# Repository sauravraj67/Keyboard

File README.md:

# Keyboard

I am making a custom keyboard for myself , it is based on 60% keyboard layout . I will also have nobs for volume and brightness control. PCB is designed in kicad and 3D covers are made in fusion.
## Features

- Base on Raspberry pico W
- Has 60% Keyboard Matrix
- Has 2 Rotor Encoder For voulem and brigtness controll 
  ### Schematic
   HOURS Worked :- 5.2 hours  <br>
So i firstly thought what would be the features of my keyboard . It is a simple mechanical keyboard in 60% layout that uses keyboard matrix so that it uses less gpio pins and diodes are used to preventing ghosting. and i will also use hot-swap so that if i want i can change the keys without soldering or de soldering. Prior to that it will has 2 rotor encoders to control the volume and brightness.

So firstly i imported all the footprints and layout of components which would be used.

Then i started with making the keyboard matrix . I used references from the web for the layout of the switches also i assigned the key sizes accordingly . I also added stabilizers for keys whose width was over 1.75 U. then i made the connection of rows and columns of the matrix .
After it i added the 2 rotor encoder ,stabilizers with required size and raspberry pi pico and made the connections of the rotor encoders to the analog pins anf colums and rows to the gpio pins.

The most time consuming part was to make the matrix because firstly you have to decide which key would be assigned to which column because after column one there are more columns then the switches over to that the sizes of each switches aren't same so i have to take a proper look on that as well . Final Look 

  ###  PCB Design  
  
   ## PCB Layout   
     HOURS Worked :- 3.5 Hours  <br>
   So i loaded the pcb with all the components again the hardest and most time consuming part was re arranging the keyboard matrix. First i added the satirizers to there responded key size , then i started arranging all the keys as per my layout at 19.05 mm and 0.7937mm grid so that the keys could easy snap with each other but many a times i had difficulties doing so , then i used different sized grides for that after i arranged all the keys then i started with arrangement of the resistors as per there connected switches in such a way that it would turn out to be a ease to me while i rout. Final look

 ## Routing    
 Hours Worked :- 3.1 <br>

I started with routing the Diodes to the swich first then after that I routed the Rows and columns and then connected it to the MCU after which I made the connections for the Rotor encoders as well . I tried to make as clean routs as possible and used both side of the PCB to rout. Somethimes there wasn;t a way to rout so I had to make some changes onto the previous rout and this ishow the final PCB looks 

<br>

### Made the case 

Hours worked :-  4.25 Hours  

So I Firstly took the dimensions of the PCB and moved to fusion for the case design firstly i started with designing the Base for that I created sketch for the base added a base height of 3mm and then moved to calculate the PCB height which will be 4.6mm (3mm for hot swap and 1.6 mm for PCB) and i added .4 mm of free space and modeled the base. Base width was 10mm less by each side in inner meserement so that the PCB can fix into in. Sketch 

BASE 

Then I updated the schematics with exact PCB dimensions so that PCB alight perfectly with the base and added holes for the screws onto it. Prior to that i extrude the base so that to fix the above components of the pcb in the base (distance from top of PCB to mid of key switch is 5mm) Top layer would be 1.1mm so i extruded 3.9mm because few components were not fitting in the Base such as the USB-B type

Then I added a hole for the USB type connection and polished the Base By curing it's side

After that i stated with making the Top layer i added the keyboard layout sketches and aligned it perfectly to the keys and made the top layer by adding them and added holes for the rotor encoder .First i thought just to add a small circular hole for the top but later i found that it would not fix well as come part of rotor encoder base was colliding with the top so i made square holes for it  . Final Look 

<br>

# Bill of Materials (BOM)

| Index | Component | Qty | Cost (USD) | Link |
|---|---|---|---|---|
| 1 | Mechanical Keyboard Switches | 2 packs | $10.62 | https://www.amazon.in/gp/product/B0G39H2G4H |
| 2 | Meckeys Shipping | 1 | $1.07 | https://meckeys.com |
| 3 | Raspberry Pi Pico SC0917 | 1 | $5.79 | https://www.amazon.in/gp/product/B0B69KZBD8 |
| 4 | Keycap Set | 1 | $10.73 | https://www.amazon.in/gp/product/B0GFNPXVJL |
| 5 | Stabilizers | 1 | $10.74 | https://meckeys.com/shop/accessories/keyboard-accessories/more/glorious-goat-stabilizers/ |
| 6 | Kailh Hot Swap Sockets | 7 packs | $5.41 | https://meckeys.com/shop/accessories/keyboard-accessories/key-switches/kailh-hot-swap-socket/ |
| 7 | PCB + Shipping (JLCPCB) | 1 | $35.98 | https://jlcpcb.com |
| 8 | Rotary Encoder | 1 pack | $1.84 | https://www.amazon.in/gp/product/B0888RWNM1 |
| 9 | Headset / Connector | 1 | $0.79 | https://www.amazon.in/gp/product/B0BB86CQSJ |
| 10 | M3 Screws | 1 | $2.20 | https://www.amazon.in/dp/B07XFP714Z |
| 11 | 3D Printed Case | 1 | 0 | Made by Cookie With Coffee from #printing-legion |

---

## Total Estimated Cost

# ~$84.17 USD

## Hardware
- Raspberry Pico 
- Cherry MX compatible Switches
- Diode
- 2 layer PCB + 3D Case
- 2 Rotor Encoder
- Hot Swap
- Key Caps

## Firmware
- It is Based on KMK and Circuit Python

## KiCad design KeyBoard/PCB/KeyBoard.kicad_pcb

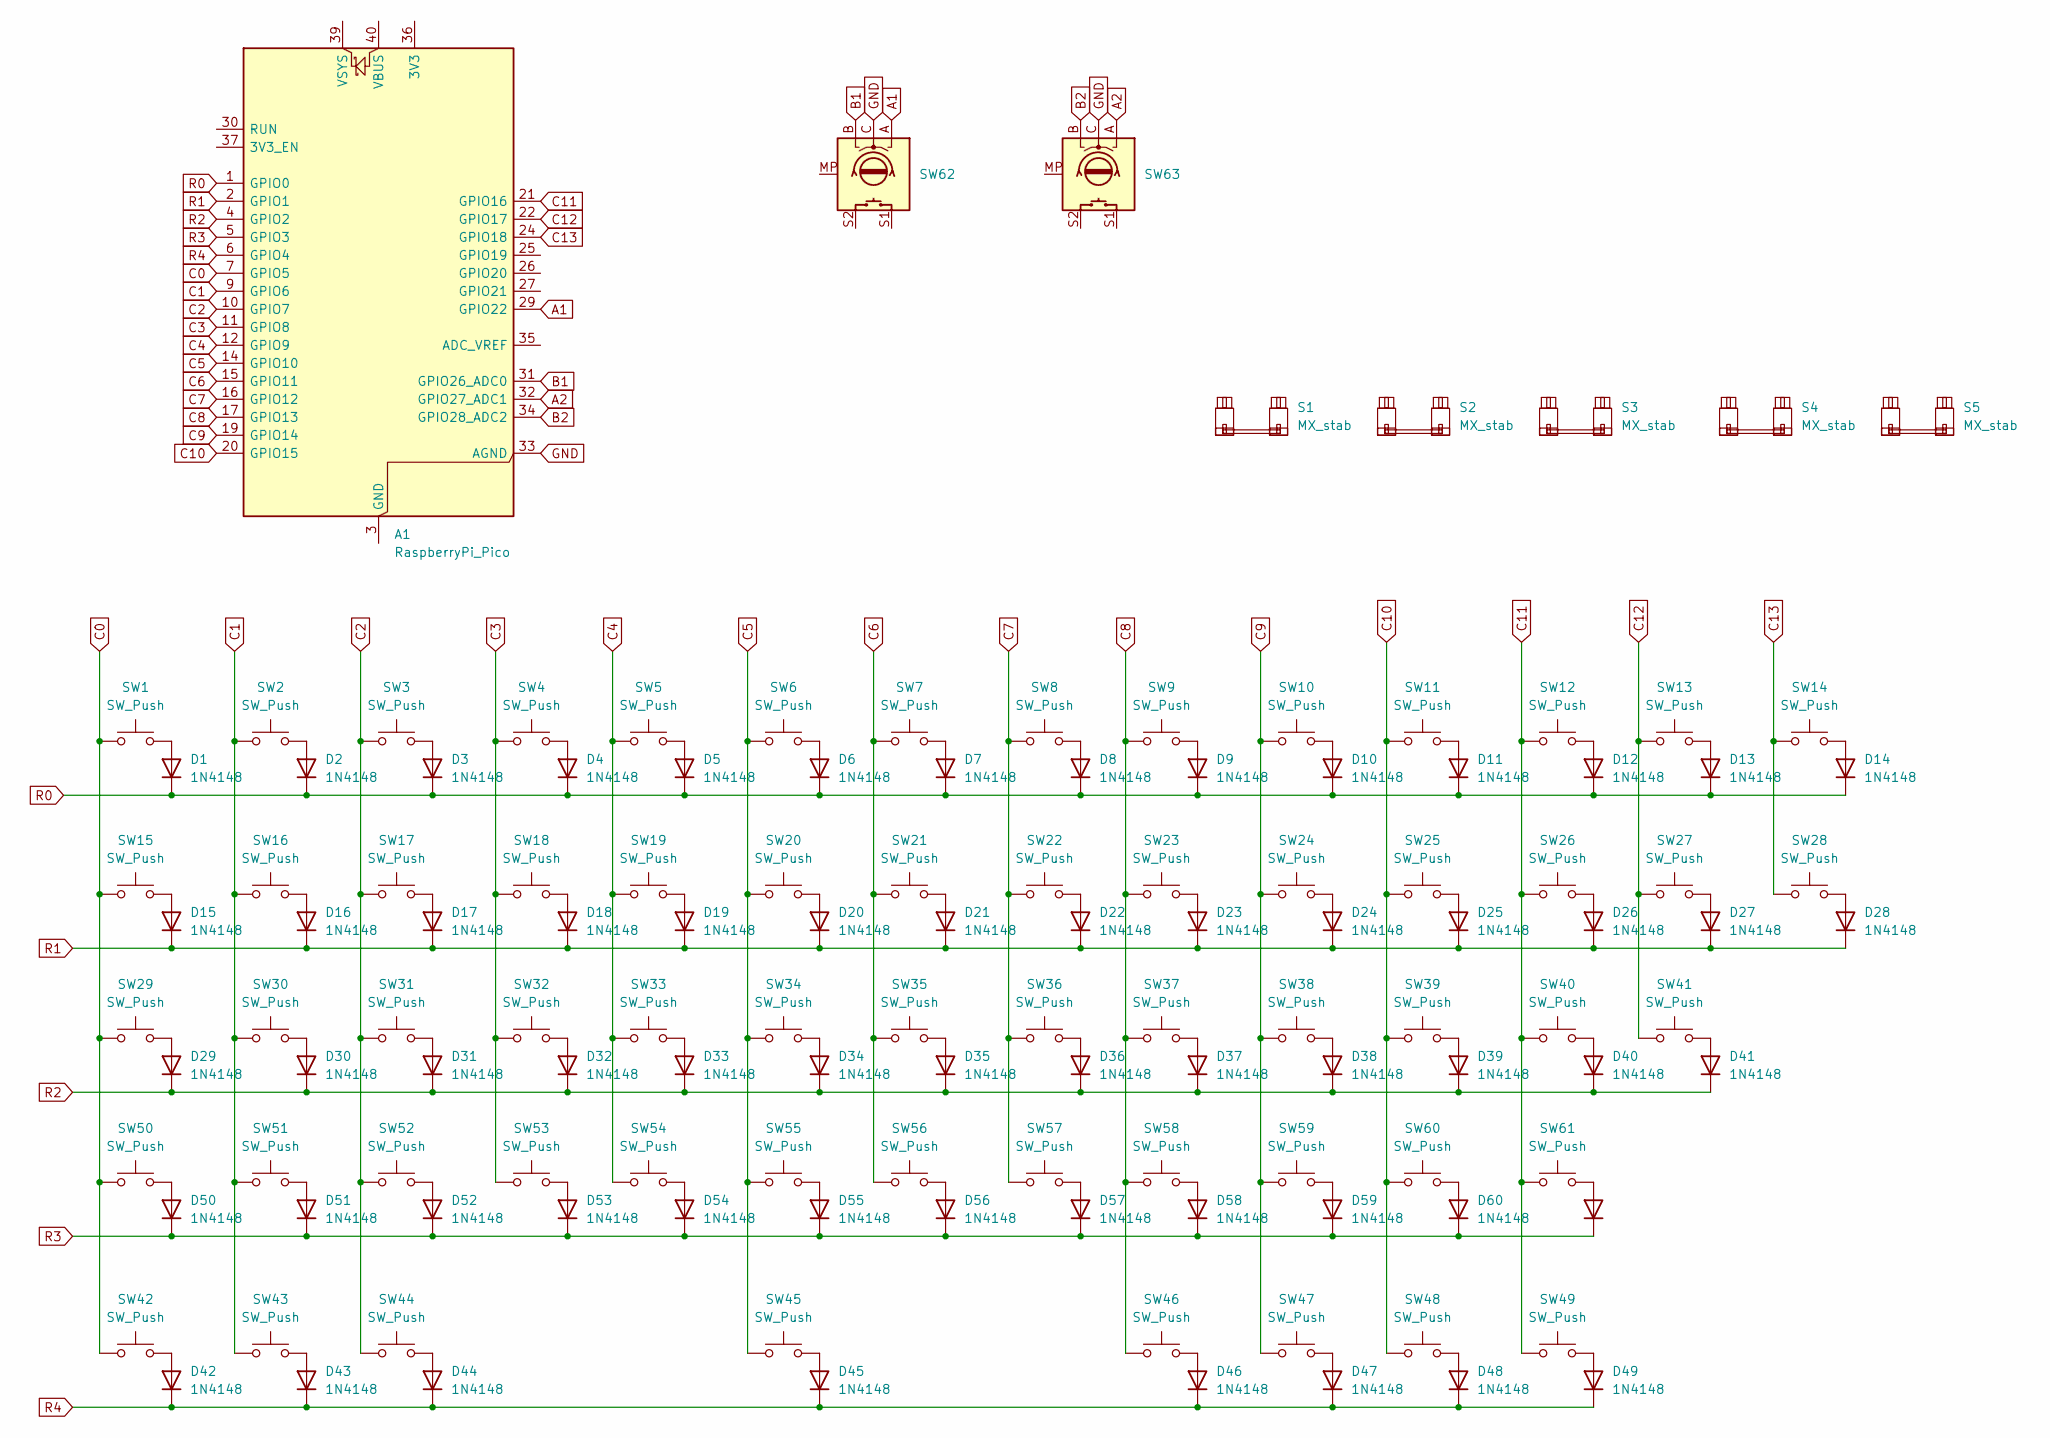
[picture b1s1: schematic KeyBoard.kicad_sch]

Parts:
A1: RaspberryPi_Pico; RaspberryPi_Pico_Common_Unspecified
D1, D2, D3, D4, D5, D6, D7, D8, D9, D10, D11, D12, D13, D14, D15, D16, D17, D18, D19, D20, D21, D22, D23, D24, D25, D26, D27, D28, D29, D30, D31, D32, D33, D34, D35, D36, D37, D38, D39, D40, D41, D42, D43, D44, D45, D46, D47, D48, D49, D50, D51, D52, D53, D54, D55, D56, D57, D58, D59, D60, D61: 1N4148; D_DO-35_SOD27_P7.62mm_Horizontal
S1: MX_stab; STAB_MX_2u
S2, S3: MX_stab; STAB_MX_2.25u
S4: MX_stab; STAB_MX_2.75u
S5: MX_stab; STAB_MX_6.25u
SW1, SW2, SW3, SW4, SW5, SW6, SW7, SW8, SW9, SW10, SW11, SW12, SW13, SW16, SW17, SW18, SW19, SW20, SW21, SW22, SW23, SW24, SW25, SW26, SW27, SW30, SW31, SW32, SW33, SW34, SW35, SW36, SW37, SW38, SW39, SW40, SW51, SW52, SW53, SW54, SW55, SW56, SW57, SW58, SW59, SW60: SW_Push; MX100H
SW14: SW_Push; MX200H
SW15, SW28: SW_Push; MX150H
SW29: SW_Push; MX175H
SW41, SW50: SW_Push; MX225HR
SW42, SW43, SW44, SW46, SW47, SW48, SW49: SW_Push; MX125H
SW45: SW_Push; MX625H
SW61: SW_Push; MX275H
SW62, SW63: RotaryEncoder_Switch_MP; RotaryEncoder_Alps_EC11E-Switch_Vertical_H20mm

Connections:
A1: A1.29 (GPIO22), SW62.A
A2: A1.32 (GPIO27_ADC1), SW63.A
B1: A1.31 (GPIO26_ADC0), SW62.B
B2: A1.34 (GPIO28_ADC2), SW63.B
C0: A1.7 (GPIO5), SW1.1, SW15.1, SW29.1, SW42.1, SW50.1
C1: A1.9 (GPIO6), SW2.1, SW16.1, SW30.1, SW43.1, SW51.1
C2: A1.10 (GPIO7), SW3.1, SW17.1, SW31.1, SW44.1, SW52.1
C3: A1.11 (GPIO8), SW4.1, SW18.1, SW32.1, SW53.1
C4: A1.12 (GPIO9), SW5.1, SW19.1, SW33.1, SW54.1
C5: A1.14 (GPIO10), SW6.1, SW20.1, SW34.1, SW45.1, SW55.1
C6: A1.15 (GPIO11), SW7.1, SW21.1, SW35.1, SW56.1
C7: A1.16 (GPIO12), SW8.1, SW22.1, SW36.1, SW57.1
C8: A1.17 (GPIO13), SW9.1, SW23.1, SW37.1, SW46.1, SW58.1
C9: A1.19 (GPIO14), SW10.1, SW24.1, SW38.1, SW47.1, SW59.1
C10: A1.20 (GPIO15), SW11.1, SW25.1, SW39.1, SW48.1, SW60.1
C11: A1.21 (GPIO16), SW12.1, SW26.1, SW40.1, SW49.1, SW61.1
C12: A1.22 (GPIO17), SW13.1, SW27.1, SW41.1
C13: A1.24 (GPIO18), SW14.1, SW28.1
GND: A1.33 (AGND), SW62.C, SW63.C
unnamed: A1.3 (GND), A1.8 (GND), A1.13 (GND), A1.18 (GND), A1.23 (GND), A1.28 (GND), A1.38 (GND)
unnamed: D1.2 (A), SW1.2
unnamed: D2.2 (A), SW2.2
unnamed: D3.2 (A), SW3.2
unnamed: D4.2 (A), SW4.2
unnamed: D5.2 (A), SW5.2
unnamed: D6.2 (A), SW6.2
unnamed: D7.2 (A), SW7.2
unnamed: D8.2 (A), SW8.2
unnamed: D9.2 (A), SW9.2
unnamed: D10.2 (A), SW10.2
unnamed: D11.2 (A), SW11.2
unnamed: D12.2 (A), SW12.2
unnamed: D13.2 (A), SW13.2
unnamed: D14.2 (A), SW14.2
unnamed: D15.2 (A), SW15.2
unnamed: D16.2 (A), SW16.2
unnamed: D17.2 (A), SW17.2
unnamed: D18.2 (A), SW18.2
unnamed: D19.2 (A), SW19.2
unnamed: D20.2 (A), SW20.2
unnamed: D21.2 (A), SW21.2
unnamed: D22.2 (A), SW22.2
unnamed: D23.2 (A), SW23.2
unnamed: D24.2 (A), SW24.2
unnamed: D25.2 (A), SW25.2
unnamed: D26.2 (A), SW26.2
unnamed: D27.2 (A), SW27.2
unnamed: D28.2 (A), SW28.2
unnamed: D29.2 (A), SW29.2
unnamed: D30.2 (A), SW30.2
unnamed: D31.2 (A), SW31.2
unnamed: D32.2 (A), SW32.2
unnamed: D33.2 (A), SW33.2
unnamed: D34.2 (A), SW34.2
unnamed: D35.2 (A), SW35.2
unnamed: D36.2 (A), SW36.2
unnamed: D37.2 (A), SW37.2
unnamed: D38.2 (A), SW38.2
unnamed: D39.2 (A), SW39.2
unnamed: D40.2 (A), SW40.2
unnamed: D41.2 (A), SW41.2
unnamed: D42.2 (A), SW42.2
unnamed: D43.2 (A), SW43.2
unnamed: D44.2 (A), SW44.2
unnamed: D45.2 (A), SW45.2
unnamed: D46.2 (A), SW46.2
unnamed: D47.2 (A), SW47.2
unnamed: D48.2 (A), SW48.2
unnamed: D49.2 (A), SW49.2
unnamed: D50.2 (A), SW50.2
unnamed: D51.2 (A), SW51.2
unnamed: D52.2 (A), SW52.2
unnamed: D53.2 (A), SW53.2
unnamed: D54.2 (A), SW54.2
unnamed: D55.2 (A), SW55.2
unnamed: D56.2 (A), SW56.2
unnamed: D57.2 (A), SW57.2
unnamed: D58.2 (A), SW58.2
unnamed: D59.2 (A), SW59.2
unnamed: D60.2 (A), SW60.2
unnamed: D61.2 (A), SW61.2
R0: A1.1 (GPIO0), D1.1 (K), D2.1 (K), D3.1 (K), D4.1 (K), D5.1 (K), D6.1 (K), D7.1 (K), D8.1 (K), D9.1 (K), D10.1 (K), D11.1 (K), D12.1 (K), D13.1 (K), D14.1 (K)
R1: A1.2 (GPIO1), D15.1 (K), D16.1 (K), D17.1 (K), D18.1 (K), D19.1 (K), D20.1 (K), D21.1 (K), D22.1 (K), D23.1 (K), D24.1 (K), D25.1 (K), D26.1 (K), D27.1 (K), D28.1 (K)
R2: A1.4 (GPIO2), D29.1 (K), D30.1 (K), D31.1 (K), D32.1 (K), D33.1 (K), D34.1 (K), D35.1 (K), D36.1 (K), D37.1 (K), D38.1 (K), D39.1 (K), D40.1 (K), D41.1 (K)
R3: A1.5 (GPIO3), D50.1 (K), D51.1 (K), D52.1 (K), D53.1 (K), D54.1 (K), D55.1 (K), D56.1 (K), D57.1 (K), D58.1 (K), D59.1 (K), D60.1 (K), D61.1 (K)
R4: A1.6 (GPIO4), D42.1 (K), D43.1 (K), D44.1 (K), D45.1 (K), D46.1 (K), D47.1 (K), D48.1 (K), D49.1 (K)

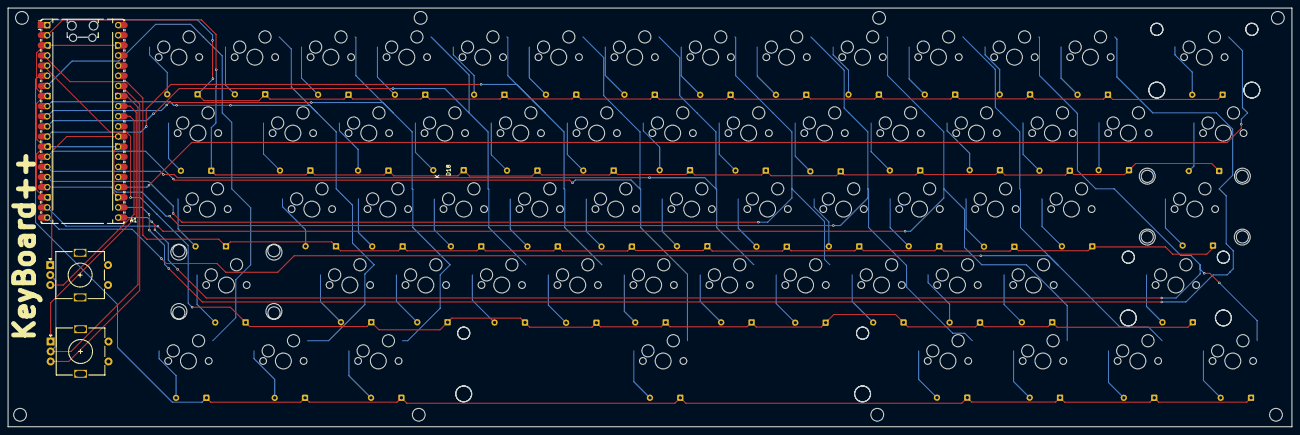
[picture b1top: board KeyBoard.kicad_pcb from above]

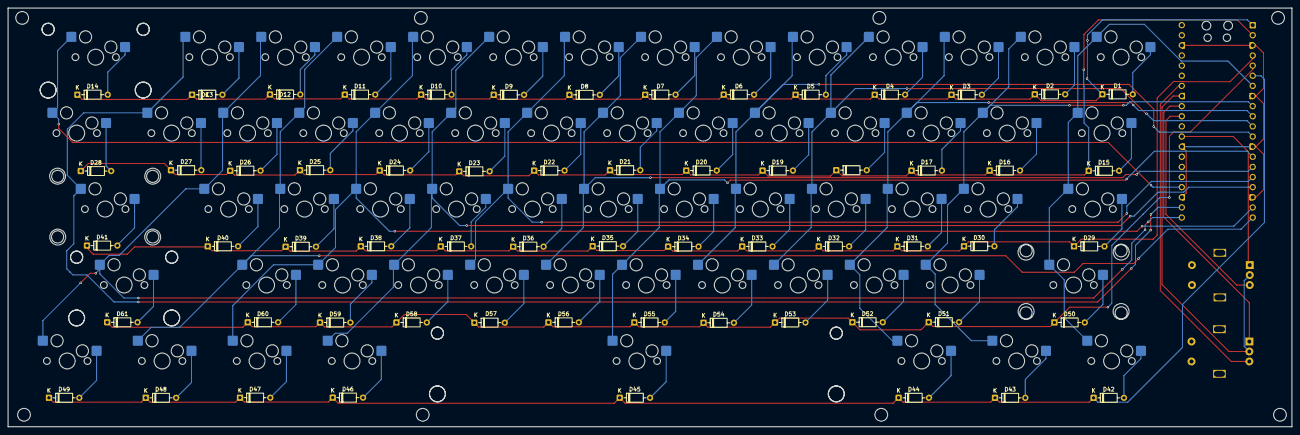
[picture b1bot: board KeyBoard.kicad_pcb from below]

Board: 2 copper layers, 322.0 x 105.0 mm, 130 parts (122 on the bottom side), 86 nets.
